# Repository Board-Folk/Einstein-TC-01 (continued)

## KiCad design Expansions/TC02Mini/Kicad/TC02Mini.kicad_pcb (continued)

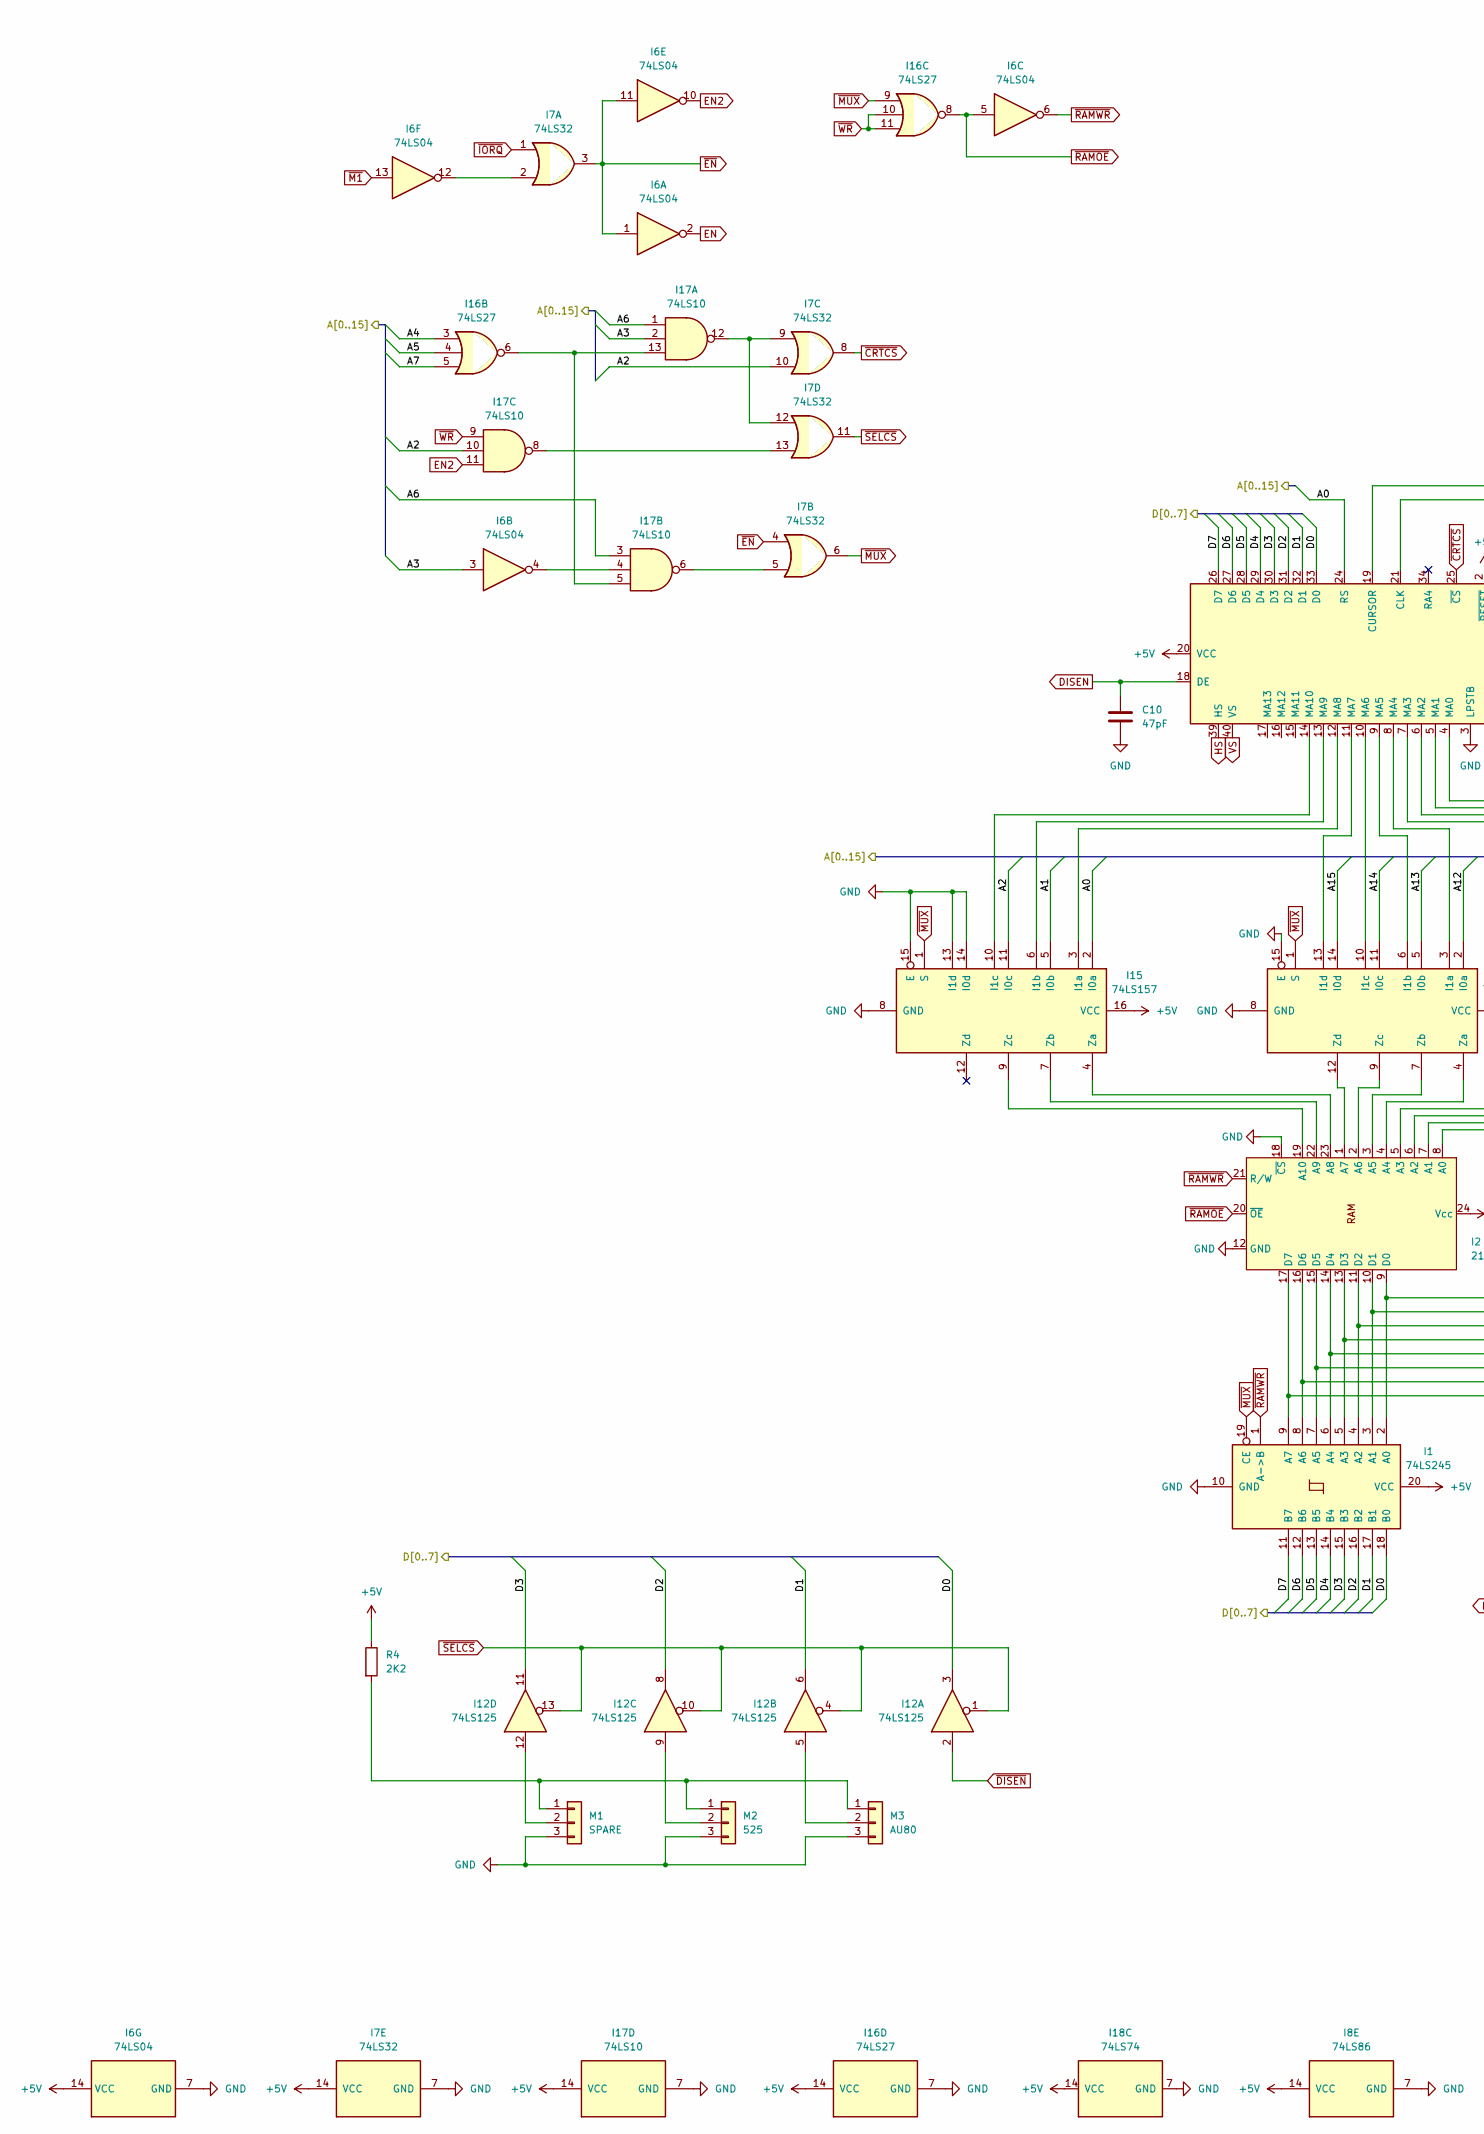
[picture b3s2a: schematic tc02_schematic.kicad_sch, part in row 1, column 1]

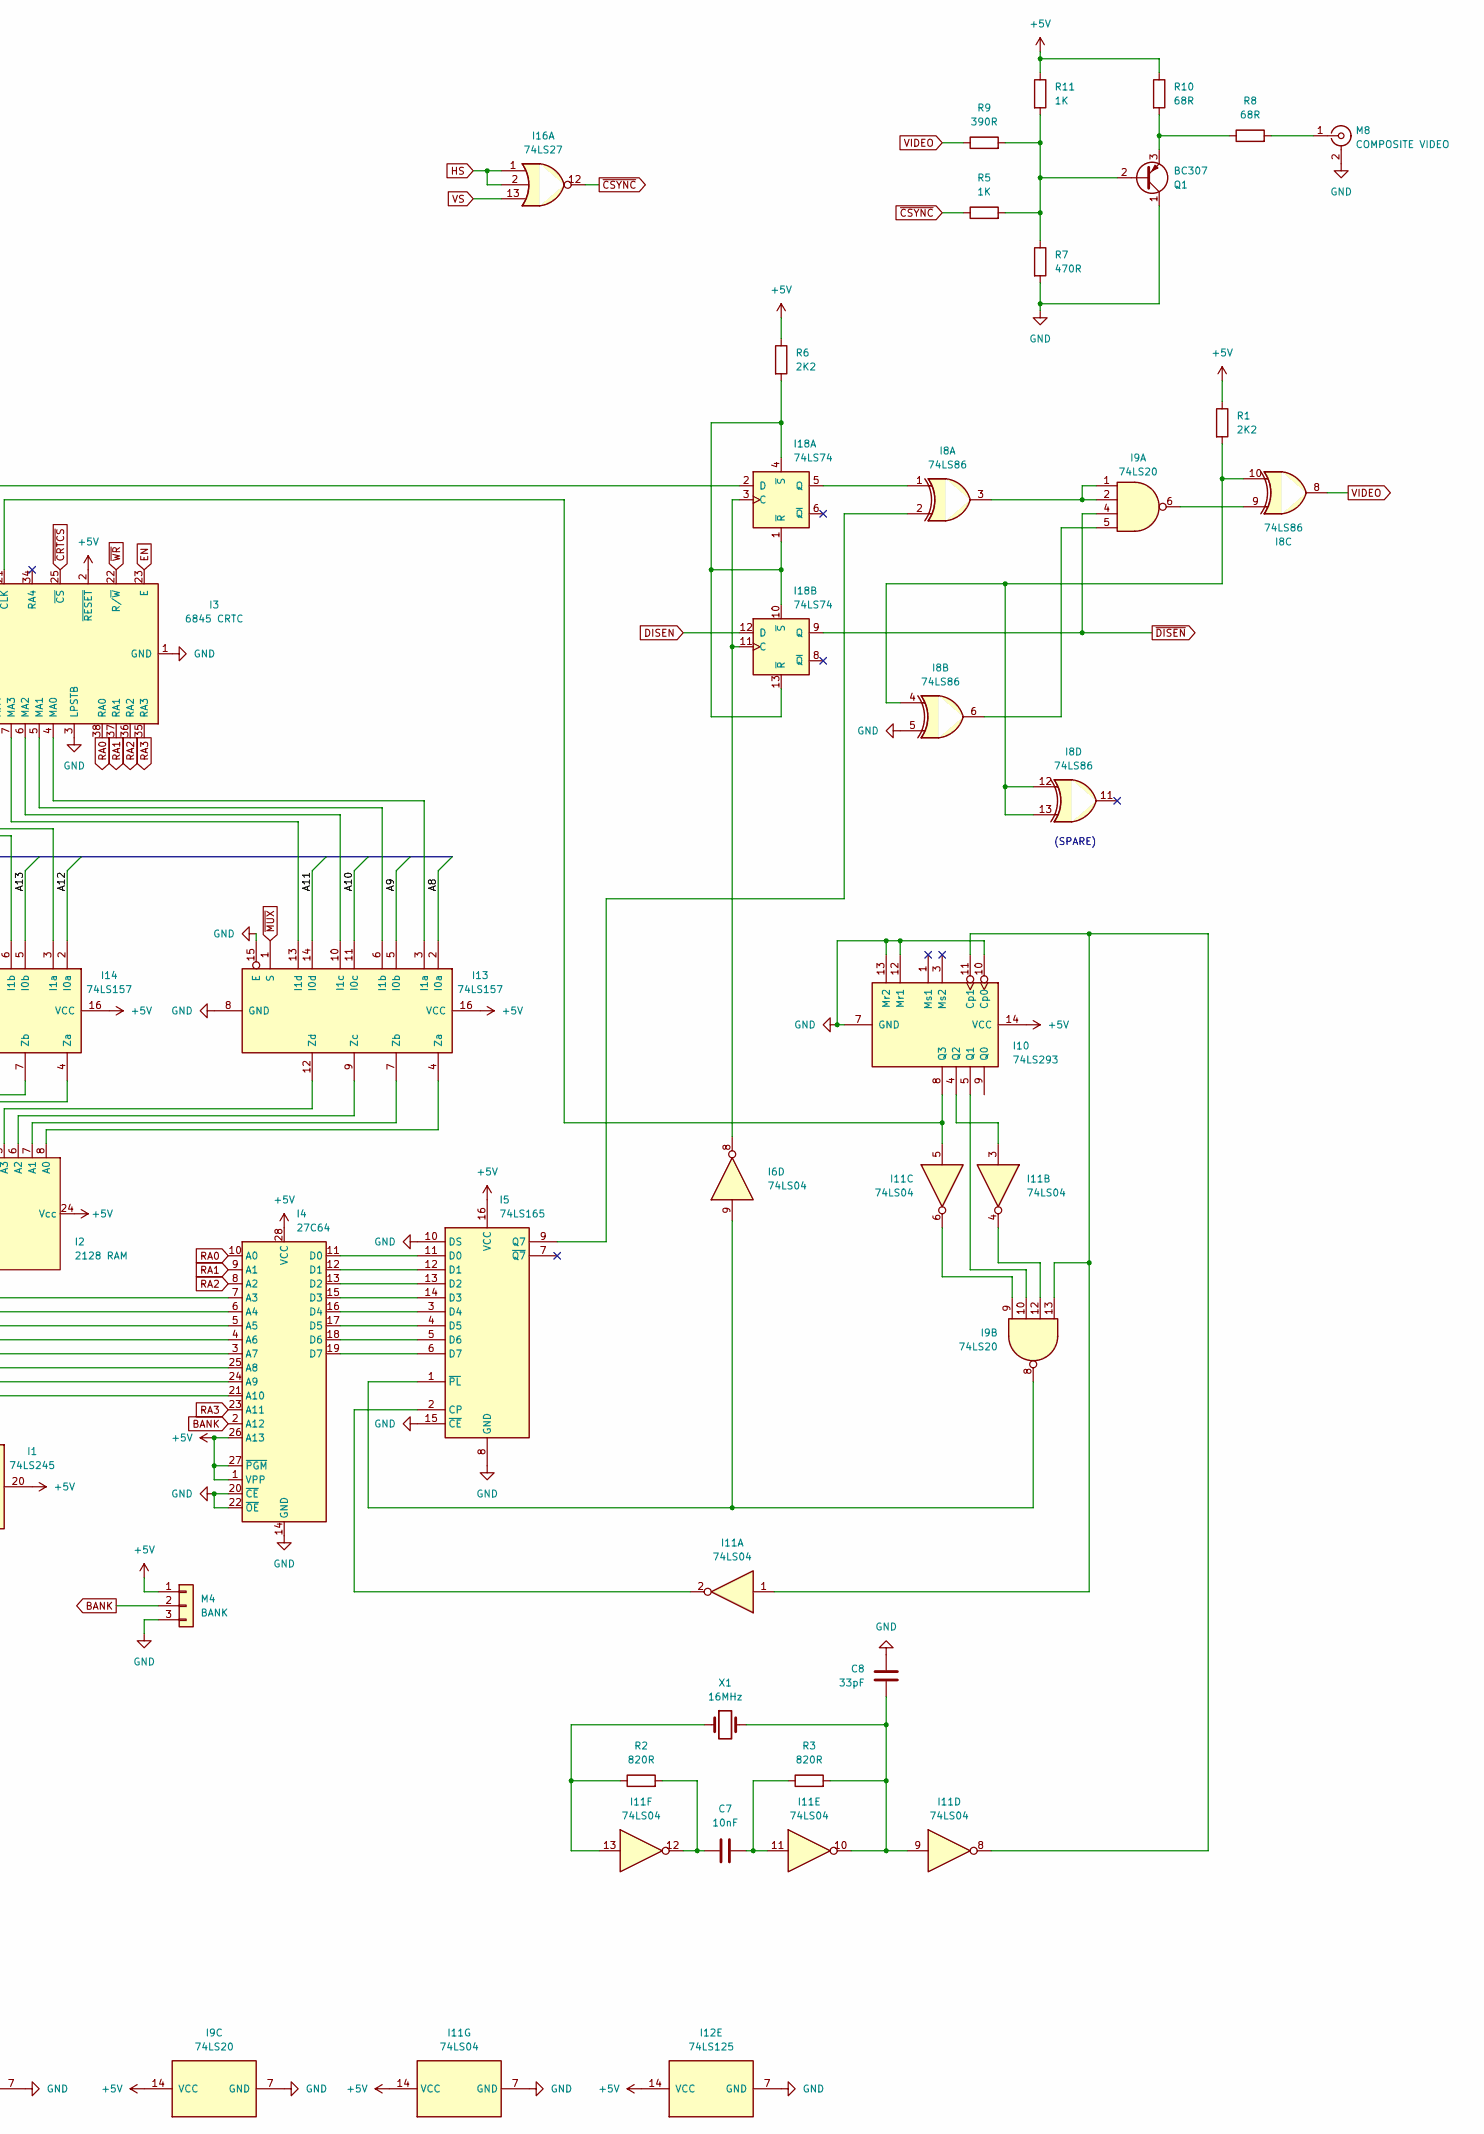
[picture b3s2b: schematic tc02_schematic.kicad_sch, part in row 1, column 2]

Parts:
C7: 10nF; C_Disc_5.08mm
C8: 33pF; C_Disc_5.08mm
C10: 47pF; C_Disc_5.08mm
I1: 74LS245; DIP-20_W7.62mm
I2: 2128 RAM; DIP-24_W15.24mm
I3: 6845 CRTC; DIP-40_W15.24mm
I4: 27C64; DIP-28_W15.24mm
I5: 74LS165; DIP-16_W7.62mm
I6, I11: 74LS04; DIP-14_W7.62mm
I7: 74LS32; DIP-14_W7.62mm
I8: 74LS86; DIP-14_W7.62mm
I9: 74LS20; DIP-14_W7.62mm
I10: 74LS293; DIP-14_W7.62mm
I12: 74LS125; DIP-14_W7.62mm
I13, I14, I15: 74LS157; DIP-16_W7.62mm
I16: 74LS27; DIP-14_W7.62mm
I17: 74LS10; DIP-14_W7.62mm
I18: 74LS74; DIP-14_W7.62mm
M1: SPARE; LK 3-Pin 2.54mm - Box
M2: 525; LK 3-Pin 2.54mm - Box
M3: AU80; LK 3-Pin 2.54mm - Box
M4: BANK; LK 3-Pin 2.54mm - Box
M8: COMPOSITE VIDEO; RCA
Q1: BC307; Transistor - Box 1 (Leg Rear)
R1, R4, R6: 2K2; Resistor 10.16mm
R2, R3: 820R; Resistor 10.16mm
R5, R11: 1K; Resistor 10.16mm
R7: 470R; Resistor 10.16mm
R8, R10: 68R; Resistor 10.16mm
R9: 390R; Resistor 10.16mm
X1: 16MHz; Crystal

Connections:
+5V: I1.20 (VCC), I2.24 (Vcc), I3.2 (~RESET), I3.20 (VCC), I4.1 (VPP), I4.26 (A13), I4.27 (~PGM), I4.28 (VCC), I5.16 (VCC), I6.14 (VCC), I7.14 (VCC), I8.14 (VCC), I9.14 (VCC), I10.14 (VCC), I11.14 (VCC), I12.14 (VCC), I13.16 (VCC), I14.16 (VCC), I15.16 (VCC), I16.14 (VCC), I17.14 (VCC), I18.14 (VCC), M4.1, R1.1, R4.1, R6.1, R10.1, R11.1; also elsewhere on the board
/80 Column Schematic/A0: I3.24 (RS), I15.2 (I0a); also elsewhere on the board
/80 Column Schematic/A1: I15.5 (I0b); also elsewhere on the board
/80 Column Schematic/A2: I7.10, I15.11 (I0c), I17.10; also elsewhere on the board
/80 Column Schematic/A3: I6.3, I17.2; also elsewhere on the board
/80 Column Schematic/A4: I16.3; also elsewhere on the board
/80 Column Schematic/A5: I16.4; also elsewhere on the board
/80 Column Schematic/A6: I17.1, I17.3; also elsewhere on the board
/80 Column Schematic/A7: I16.5; also elsewhere on the board
/80 Column Schematic/A8: I13.2 (I0a); also elsewhere on the board
/80 Column Schematic/A9: I13.5 (I0b); also elsewhere on the board
/80 Column Schematic/A10: I13.11 (I0c); also elsewhere on the board
/80 Column Schematic/A11: I13.14 (I0d); also elsewhere on the board
/80 Column Schematic/A12: I14.2 (I0a); also elsewhere on the board
/80 Column Schematic/A13: I14.5 (I0b); also elsewhere on the board
/80 Column Schematic/A14: I14.11 (I0c); also elsewhere on the board
/80 Column Schematic/A15: I14.14 (I0d); also elsewhere on the board
/80 Column Schematic/D0: I1.18 (B0), I3.33 (D0), I12.3; also elsewhere on the board
/80 Column Schematic/D1: I1.17 (B1), I3.32 (D1), I12.6; also elsewhere on the board
/80 Column Schematic/D2: I1.16 (B2), I3.31 (D2), I12.8; also elsewhere on the board
/80 Column Schematic/D3: I1.15 (B3), I3.30 (D3), I12.11; also elsewhere on the board
/80 Column Schematic/D4: I1.14 (B4), I3.29 (D4); also elsewhere on the board
/80 Column Schematic/D5: I1.13 (B5), I3.28 (D5); also elsewhere on the board
/80 Column Schematic/D6: I1.12 (B6), I3.27 (D6); also elsewhere on the board
/80 Column Schematic/D7: I1.11 (B7), I3.26 (D7); also elsewhere on the board
BANK: I4.2 (A12), M4.2
DISEN: C10.1, I3.18 (DE), I18.12 (D)
EN: I3.23 (E), I6.2
EN2: I6.10, I17.11
GND: C8.1, C10.2, I1.10 (GND), I2.12 (GND), I2.18 (~CS), I3.1 (GND), I3.3 (LPSTB), I4.14 (GND), I4.20 (~CE), I4.22 (~OE), I5.8 (GND), I5.10 (DS), I5.15 (~CE), I6.7 (GND), I7.7 (GND), I8.5, I8.7 (GND), I9.7 (GND), I10.7 (GND), I10.10 (Cp0), I10.12 (Mr1), I10.13 (Mr2), I11.7 (GND), I12.7 (GND), I13.8 (GND), I13.15 (E), I14.8 (GND), I14.15 (E), I15.8 (GND), I15.13 (I1d), I15.14 (I0d), I15.15 (E), I16.7 (GND), I17.7 (GND), I18.7 (GND), M1.3, M2.3, M3.3, M4.3, M8.2 (Ext), Q1.1 (C), R7.2; also elsewhere on the board
HS: I3.39 (HS), I16.1, I16.2
unnamed: C7.1, I11.12, R2.2
unnamed: C7.2, I11.11, R3.1
unnamed: C8.2, I11.9, I11.10, R3.2, X1.2
unnamed: I1.2 (A0), I2.9 (D0), I4.7 (A3)
unnamed: I1.3 (A1), I2.10 (D1), I4.6 (A4)
unnamed: I1.4 (A2), I2.11 (D2), I4.5 (A5)
unnamed: I1.5 (A3), I2.13 (D3), I4.4 (A6)
unnamed: I1.6 (A4), I2.14 (D4), I4.3 (A7)
unnamed: I1.7 (A5), I2.15 (D5), I4.25 (A8)
unnamed: I1.8 (A6), I2.16 (D6), I4.24 (A9)
unnamed: I1.9 (A7), I2.17 (D7), I4.21 (A10)
unnamed: I4.11 (D0), I5.11 (D0)
unnamed: I4.12 (D1), I5.12 (D1)
unnamed: I4.13 (D2), I5.13 (D2)
unnamed: I4.15 (D3), I5.14 (D3)
unnamed: I4.16 (D4), I5.3 (D4)
unnamed: I4.17 (D5), I5.4 (D5)
unnamed: I4.18 (D6), I5.5 (D6)
unnamed: I4.19 (D7), I5.6 (D7)
unnamed: I5.2 (CP), I11.2
unnamed: I5.9 (Q7), I8.2
unnamed: I5.1 (~PL), I6.9, I9.8
unnamed: I6.12, I7.2
unnamed: I8.3, I9.1, I9.2
unnamed: I8.6, I9.5
unnamed: I8.9, I9.6
unnamed: I8.4, I8.10, I8.12, I8.13, R1.2
unnamed: I9.13, I10.11 (Cp1), I11.1, I11.8
unnamed: I9.10, I10.5 (Q1)
unnamed: I10.4 (Q2), I11.3
unnamed: I3.21 (CLK), I10.8 (Q3), I11.5
unnamed: I9.12, I11.4
unnamed: I9.9, I11.6
unnamed: I11.13, R2.1, X1.1
unnamed: I3.4 (MA0), I13.3 (I1a)
unnamed: I3.5 (MA1), I13.6 (I1b)
unnamed: I3.6 (MA2), I13.10 (I1c)
unnamed: I3.7 (MA3), I13.13 (I1d)
unnamed: I2.8 (A0), I13.4 (Za)
unnamed: I2.7 (A1), I13.7 (Zb)
unnamed: I2.6 (A2), I13.9 (Zc)
unnamed: I2.5 (A3), I13.12 (Zd)
unnamed: I3.8 (MA4), I14.3 (I1a)
unnamed: I3.9 (MA5), I14.6 (I1b)
unnamed: I3.10 (MA6), I14.10 (I1c)
unnamed: I3.11 (MA7), I14.13 (I1d)
unnamed: I2.4 (A4), I14.4 (Za)
unnamed: I2.3 (A5), I14.7 (Zb)
unnamed: I2.2 (A6), I14.9 (Zc)
unnamed: I2.1 (A7), I14.12 (Zd)
unnamed: I3.12 (MA8), I15.3 (I1a)
unnamed: I3.13 (MA9), I15.6 (I1b)
unnamed: I3.14 (MA10), I15.10 (I1c)
unnamed: I2.23 (A8), I15.4 (Za)
unnamed: I2.22 (A9), I15.7 (Zb)
unnamed: I2.19 (A10), I15.9 (Zc)
unnamed: I16.6, I17.5, I17.13
unnamed: I6.4, I17.4
unnamed: I7.5, I17.6
unnamed: I7.13, I17.8
unnamed: I7.9, I7.12, I17.12
unnamed: I6.8, I18.3 (C), I18.11 (C)
unnamed: I3.19 (CURSOR), I18.2 (D)
unnamed: I8.1, I18.5 (Q)
unnamed: I18.1 (~R), I18.4 (~S), I18.10 (~S), I18.13 (~R), R6.2
unnamed: M1.1, M2.1, M3.1, R4.2
unnamed: I12.12, M1.2
unnamed: I12.9, M2.2
unnamed: I12.5, M3.2
unnamed: M8.1 (In), R8.2
unnamed: Q1.2 (B), R5.2, R7.1, R9.2, R11.2
unnamed: Q1.3 (E), R8.1, R10.2
RA0: I3.38 (RA0), I4.10 (A0)
RA1: I3.37 (RA1), I4.9 (A1)
RA2: I3.36 (RA2), I4.8 (A2)
RA3: I3.35 (RA3), I4.23 (A11)
VIDEO: I8.8, R9.1
VS: I3.40 (VS), I16.13
~CRTCS: I3.25 (~CS), I7.8
~CSYNC: I16.12, R5.1
~DISEN: I9.4, I12.2, I18.9 (Q)
~EN: I6.1, I6.11, I7.3, I7.4
~IORQ: I7.1; also elsewhere on the board
~M1: I6.13; also elsewhere on the board
~MUX: I1.19 (CE), I7.6, I13.1 (S), I14.1 (S), I15.1 (S), I16.9
~RAMOE: I2.20 (~OE), I6.5, I16.8
~RAMWR: I1.1 (A->B), I2.21 (R/W), I6.6
~SELCS: I7.11, I12.1, I12.4, I12.10, I12.13
~WR: I3.22 (R/~W), I16.10, I16.11, I17.9; also elsewhere on the board

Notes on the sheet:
(SPARE)

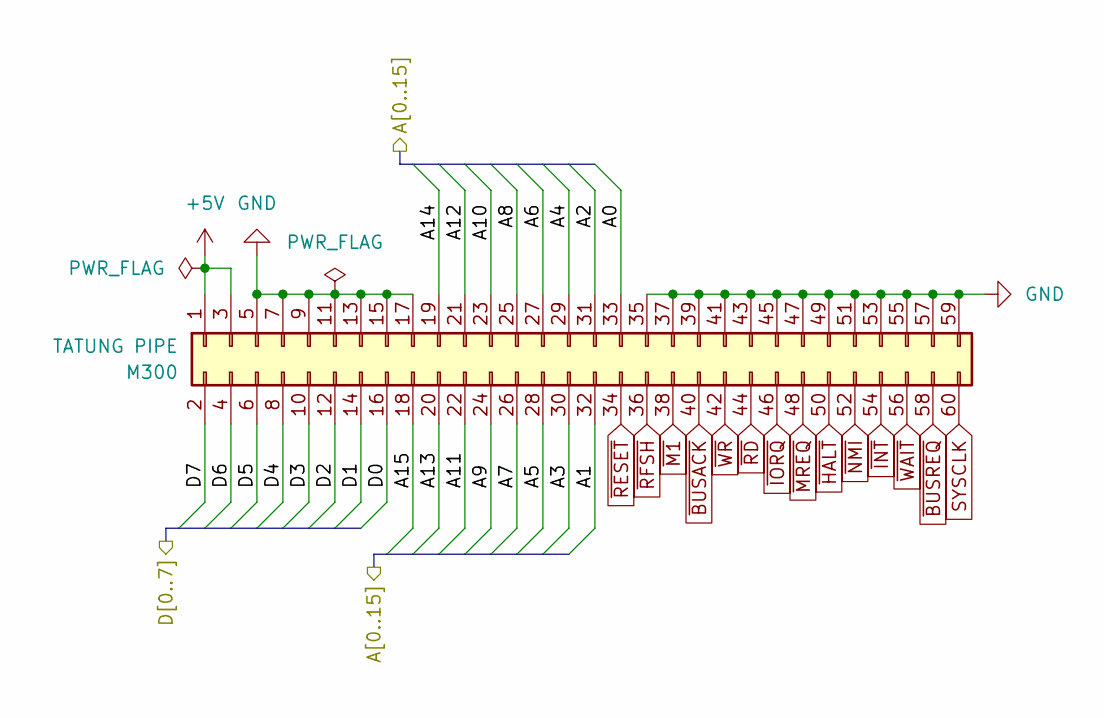
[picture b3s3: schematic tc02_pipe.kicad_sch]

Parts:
M300: TATUNG PIPE; M3 PinHeader_2x30_P2.54mm

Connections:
+5V: M300.1, M300.3; also elsewhere on the board
/80 Column Schematic/A0: M300.33; also elsewhere on the board
/80 Column Schematic/A1: M300.32; also elsewhere on the board
/80 Column Schematic/A2: M300.31; also elsewhere on the board
/80 Column Schematic/A3: M300.30; also elsewhere on the board
/80 Column Schematic/A4: M300.29; also elsewhere on the board
/80 Column Schematic/A5: M300.28; also elsewhere on the board
/80 Column Schematic/A6: M300.27; also elsewhere on the board
/80 Column Schematic/A7: M300.26; also elsewhere on the board
/80 Column Schematic/A8: M300.25; also elsewhere on the board
/80 Column Schematic/A9: M300.24; also elsewhere on the board
/80 Column Schematic/A10: M300.23; also elsewhere on the board
/80 Column Schematic/A11: M300.22; also elsewhere on the board
/80 Column Schematic/A12: M300.21; also elsewhere on the board
/80 Column Schematic/A13: M300.20; also elsewhere on the board
/80 Column Schematic/A14: M300.19; also elsewhere on the board
/80 Column Schematic/A15: M300.18; also elsewhere on the board
/80 Column Schematic/D0: M300.16; also elsewhere on the board
/80 Column Schematic/D1: M300.14; also elsewhere on the board
/80 Column Schematic/D2: M300.12; also elsewhere on the board
/80 Column Schematic/D3: M300.10; also elsewhere on the board
/80 Column Schematic/D4: M300.8; also elsewhere on the board
/80 Column Schematic/D5: M300.6; also elsewhere on the board
/80 Column Schematic/D6: M300.4; also elsewhere on the board
/80 Column Schematic/D7: M300.2; also elsewhere on the board
GND: M300.5, M300.7, M300.9, M300.11, M300.13, M300.15, M300.17, M300.35, M300.37, M300.39, M300.41, M300.43, M300.45, M300.47, M300.49, M300.51, M300.53, M300.55, M300.57, M300.59; also elsewhere on the board
SYSCLK: M300.60
~BUSACK: M300.40
~BUSREQ: M300.58
~HALT: M300.50
~INT: M300.54
~IORQ: M300.46; also elsewhere on the board
~M1: M300.38; also elsewhere on the board
~MREQ: M300.48
~NMI: M300.52
~RD: M300.44
~RESET: M300.34
~RFSH: M300.36
~WAIT: M300.56
~WR: M300.42; also elsewhere on the board

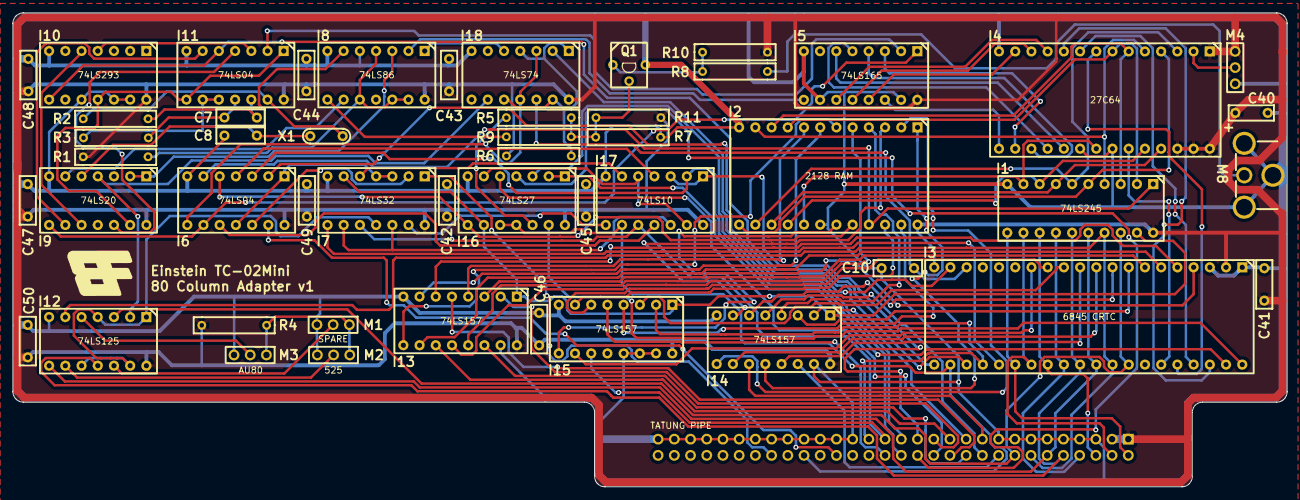
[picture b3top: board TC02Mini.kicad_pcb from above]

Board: 2 copper layers, 199.6 x 74.2 mm, 52 parts (0 on the bottom side), 120 nets.
